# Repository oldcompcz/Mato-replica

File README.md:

# Mato-replica
Mato computer replica

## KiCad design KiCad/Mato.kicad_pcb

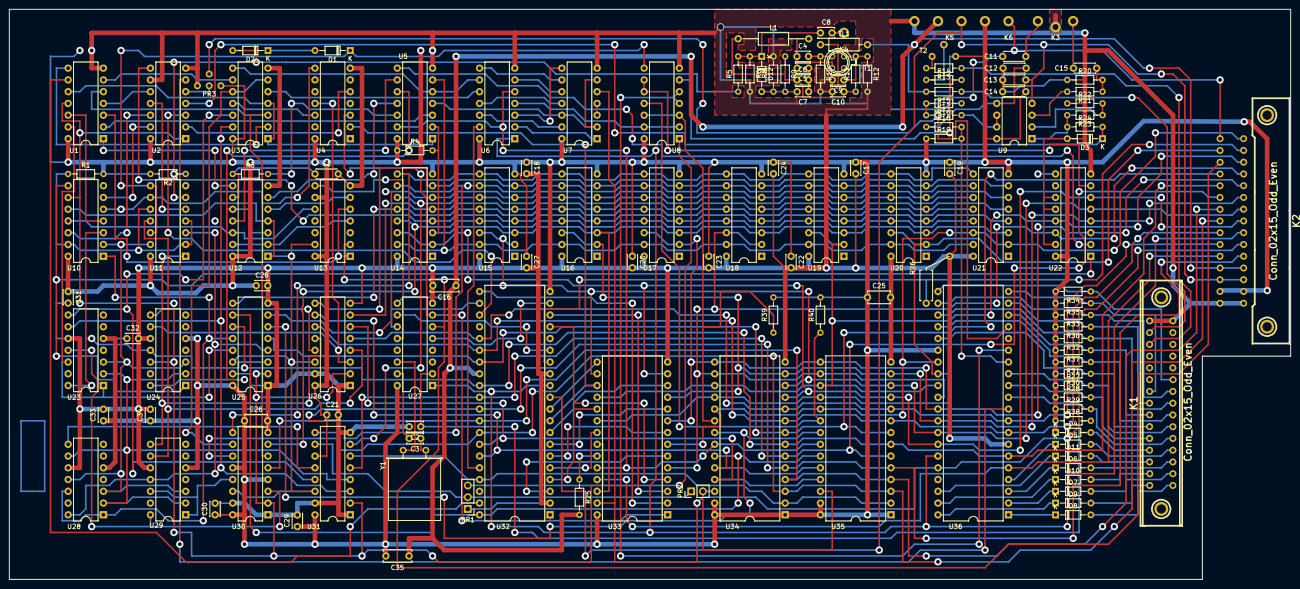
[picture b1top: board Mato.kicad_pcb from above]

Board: 4 copper layers, 276.9 x 123.2 mm, 136 parts (0 on the bottom side), 184 nets.

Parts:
C1: 220p; C_Disc_D4.3mm_W1.9mm_P5.00mm
C2: 1M; C_Disc_D3.4mm_W2.1mm_P2.50mm
C3: 8p2; C_Disc_D3.4mm_W2.1mm_P2.50mm
C4: 6p8; C_Disc_D3.0mm_W2.0mm_P2.50mm
C5: 18p; C_Disc_D3.0mm_W2.0mm_P2.50mm
C6: 10p; C_Disc_D3.0mm_W2.0mm_P2.50mm
C7: 2p2; C_Disc_D3.0mm_W2.0mm_P2.50mm
C8: 22p; C_Disc_D3.4mm_W2.1mm_P2.50mm
C9: 100p; C_Disc_D3.0mm_W2.0mm_P2.50mm
C10: 3n3; C_Disc_D3.0mm_W2.0mm_P2.50mm
C11: M1; C_Disc_D4.3mm_W1.9mm_P5.00mm
C12, C13, C14: 100n; C_Disc_D4.3mm_W1.9mm_P5.00mm
C15: 1M; C_Disc_D4.3mm_W1.9mm_P5.00mm
C16, C35: 68n; C_Disc_D6.0mm_W2.5mm_P5.00mm
C17, C18, C19, C20, C21, C22, C23, C24, C27, C28, C34: 68n; C_Disc_D3.0mm_W2.0mm_P2.50mm
C25, C26: 68n; C_Disc_D4.7mm_W2.5mm_P5.00mm
C29, C30, C31, C32, C33: CP; C_Disc_D3.0mm_W2.0mm_P2.50mm
D1, D2, D6, D7, D8, D9, D10, D11: D; D_DO-34_SOD68_P7.62mm_Horizontal
D3, D4: KA261; D_DO-34_SOD68_P7.62mm_Horizontal
D5: 7 x KA 261; D_DO-34_SOD68_P7.62mm_Horizontal
D12: KA206; D_DO-34_SOD68_P7.62mm_Horizontal
K1: Conn_02x15_Odd_Even; TX5133012-mato
K2: Conn_02x15_Odd_Even; TX5133011-mato
K3: K3; mato-K3
K4: Conn_01x02_Female; mato-K6
K5: Power; mato-power
K6: K6; mato-K6
L1: L; R_Axial_DIN0207_L6.3mm_D2.5mm_P15.24mm_Horizontal
PR1: mato-pr1; PinHeader_1x03_P2.54mm_Vertical
PR2: Jumper_NO_Small; PinHeader_1x02_P2.54mm_Vertical
PR3: 4-point-link; mato-pr3
R1: 2K7; R_Axial_DIN0204_L3.6mm_D1.6mm_P7.62mm_Horizontal
R2: 470R; R_Axial_DIN0204_L3.6mm_D1.6mm_P7.62mm_Horizontal
R3: 100R; R_Axial_DIN0204_L3.6mm_D1.6mm_P7.62mm_Horizontal
R4: 270R; R_Axial_DIN0204_L3.6mm_D1.6mm_P7.62mm_Horizontal
R5: 1K2; R_Axial_DIN0204_L3.6mm_D1.6mm_P7.62mm_Horizontal
R6, R10, R14, R16, R18, R19, R22, R25, R39, R40: 1K; R_Axial_DIN0204_L3.6mm_D1.6mm_P7.62mm_Horizontal
R8: 6K8; R_Axial_DIN0204_L3.6mm_D1.6mm_P7.62mm_Horizontal
R9, R27, R28, R29, R30, R31, R32, R33, R34, R35, R36, R37: 18K; R_Axial_DIN0204_L3.6mm_D1.6mm_P7.62mm_Horizontal
R11: 8K2; R_Axial_DIN0204_L3.6mm_D1.6mm_P7.62mm_Horizontal
R12: 2K2; R_Axial_DIN0204_L3.6mm_D1.6mm_P7.62mm_Horizontal
R13: 56R; R_Axial_DIN0204_L3.6mm_D1.6mm_P7.62mm_Horizontal
R15: 180R; R_Axial_DIN0204_L3.6mm_D1.6mm_P7.62mm_Horizontal
R17, R20: 10K; R_Axial_DIN0204_L3.6mm_D1.6mm_P7.62mm_Horizontal
R21: 4K7; R_Axial_DIN0204_L3.6mm_D1.6mm_P7.62mm_Horizontal
R23: 82K; R_Axial_DIN0204_L3.6mm_D1.6mm_P7.62mm_Horizontal
R24: 130; R_Axial_DIN0204_L3.6mm_D1.6mm_P7.62mm_Horizontal
R26: 270R; R_Axial_Bend
R38: M22; R_Axial_DIN0204_L3.6mm_D1.6mm_P7.62mm_Horizontal
T1: KF 524; KF524
T2: KC 307; mato-kc307
TL1: L; R_Axial_DIN0207_L6.3mm_D2.5mm_P10.16mm_Horizontal
U1, U6: 7404; DIP-14_W7.62mm
U2: 7486; DIP-14_W7.62mm
U3, U7, U12: 7400; DIP-14_W7.62mm
U4: 7474; DIP-14_W7.62mm
U5, U10: 7410; DIP-14_W7.62mm
U8: 7403; DIP-14_W7.62mm
U9: LM1458; DIP-8_W7.62mm
U11: 7405; DIP-14_W7.62mm
U13: 74164; DIP-14_W7.62mm
U14, U15, U16, U17, U18, U19, U20, U21: 4164; DIP-16_W7.62mm
U22: 74165; DIP-16_W7.62mm
U23, U24, U28, U29: 7493; DIP-14_W7.62mm
U25, U26, U30, U31: 74153; DIP-16_W7.62mm
U27: 8224; DIP-16_W7.62mm
U32: 8080A; DIP-40_W15.24mm
U33: 8228; DIP-28_W15.24mm
U34, U35: 27C64/128; DIP-28_W15.24mm
U36: 8255; DIP-40_W15.24mm
Y1: Crystal; Crystal_HC18-U_Horizontal

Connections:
+5V: C14.2, C17.1, C18.1, C19.1, C20.1, C21.1, C22.1, C23.1, C24.1, C25.1, C26.1, C27.1, C28.1, C29.1, C30.1, C31.1, C32.1, C33.1, C34.1, C35.2, D4.1, K2.27, K2.28, K5.4, PR3.6, R1.2, R2.2, R4.1, R15.2, R19.1, R27.1, R28.1, R29.1, R30.2, R31.2, R32.2, R33.2, R34.2, R35.2, R36.2, R37.2, R38.1, R39.2, R40.2, T2.3, TL1.2, U1.14, U2.14, U3.14, U4.14, U5.14, U6.14, U7.14, U8.14, U9.8, U10.14, U11.14, U12.14, U13.9, U13.14, U14.8, U15.8, U16.8, U17.8, U18.8, U19.8, U20.8, U21.8, U22.16, U23.5, U24.5, U25.16, U26.16, U27.16, U28.5, U29.5, U30.4, U30.12, U30.16, U31.16, U32.20, U33.28, U34.1, U34.27, U34.28, U35.1, U35.27, U35.28, U36.26
+12V: C16.1, C35.1, K2.23, K2.24, K5.2, R25.2, U27.9, U32.28
-5V: C13.2, K2.25, K2.26, K5.3, U9.4, U32.11
/PIO/CONT: K1.21, R29.2, U36.11
/PIO/LED1: K1.4, R15.1
/PIO/REPRO: K1.6, R13.1
/PIO/SHIFT: K1.22, R28.2, U36.12
/PIO/STOP: K1.19, R27.2, U36.13
/RAM/addr0: U14.5, U15.5, U16.5, U17.5, U18.5, U19.5, U20.5, U21.5, U26.7
/RAM/addr1: U14.7, U15.7, U16.7, U17.7, U18.7, U19.7, U20.7, U21.7, U26.9
/RAM/addr2: U14.6, U15.6, U16.6, U17.6, U18.6, U19.6, U20.6, U21.6, U25.7
/RAM/addr3: U14.12, U15.12, U16.12, U17.12, U18.12, U19.12, U20.12, U21.12, U25.9
/RAM/addr4: U14.11, U15.11, U16.11, U17.11, U18.11, U19.11, U20.11, U21.11, U31.7
/RAM/addr5: U14.10, U15.10, U16.10, U17.10, U18.10, U19.10, U20.10, U21.10, U31.9
/RAM/addr6: U14.13, U15.13, U16.13, U17.13, U18.13, U19.13, U20.13, U21.13, U30.7
/RAM/addr7: U14.9, U15.9, U16.9, U17.9, U18.9, U19.9, U20.9, U21.9, U30.9
/READY: U2.3, U32.23
/STSTB: U4.3, U27.7, U33.1
/SYNC: U27.5, U32.19
/modulator/TV-VIDEO: C8.2, K4.1
A0: K2.20, U26.5, U32.25, U34.10, U35.10, U36.9
A1: K2.18, U26.11, U32.26, U34.9, U35.9, U36.8
A2: K2.8, U25.5, U32.27, U34.8, U35.8
A3: K2.10, U25.11, U32.29, U34.7, U35.7, U36.6
A4: K2.12, U31.5, U32.30, U34.6, U35.6
A5: K2.21, U31.11, U32.31, U34.5, U35.5
A6: K2.14, U30.5, U32.32, U34.4, U35.4
A7: K2.16, U30.11, U32.33, U34.3, U35.3
A8: U26.6, U32.34, U34.25, U35.25
A9: U26.10, U32.35, U34.24, U35.24
A10: U25.6, U32.1, U34.21, U35.21
A11: U25.10, U32.40, U34.23, U35.23
A12: U31.6, U32.37, U34.2, U35.2
A13: PR1.2, PR2.1, U31.10, U32.38
A14: U1.9, U32.39
A14*: U1.5, U3.3, U30.6
A15: U6.13, U32.36
A15*: U3.6, U3.10, U30.10
CAS: U5.10, U12.3, U12.10, U24.14
COMPOSITE: D2.2, R2.1, R5.1, U11.6
CSROM0: R40.1, U8.11, U35.20
CSROM1: R39.1, U8.3, U8.12, U34.20
D0: K2.15, U14.2, U14.14, U22.6, U33.13, U34.11, U35.11, U36.34
D1: K2.13, U15.2, U15.14, U22.5, U33.16, U34.12, U35.12, U36.33
D2: K2.11, U16.2, U16.14, U22.4, U33.11, U34.13, U35.13, U36.32
D3: K2.9, U17.2, U17.14, U22.3, U33.9, U34.15, U35.15, U36.31
D4: K2.7, U18.2, U18.14, U22.14, U33.5, U34.16, U35.16, U36.30
D5: K2.5, U19.2, U19.14, U22.13, U33.18, U34.17, U35.17, U36.29
D6: K2.4, U20.2, U20.14, U33.20, U34.18, U35.18, U36.28
D7: K2.1, U21.2, U21.14, U33.7, U34.19, U35.19, U36.27
GND: C1.2, C2.2, C9.2, C10.2, C12.2, C13.1, C14.1, C16.2, C17.2, C18.2, C19.2, C20.2, C21.2, C22.2, C23.2, C24.2, C25.2, C26.2, C27.2, C28.2, C29.2, C30.2, C31.2, C32.2, C33.2, C34.2, D3.2, K1.1, K1.2, K2.29, K2.30, K3.3, K5.1, PR1.1, PR3.4, R6.2, R8.2, R10.2, R12.2, R16.1, R20.1, R22.1, R26.2, U1.7, U2.7, U2.9, U3.7, U4.7, U5.7, U6.7, U7.7, U8.7, U10.7, U11.7, U12.7, U13.7, U14.16, U15.16, U16.16, U17.16, U18.16, U19.16, U20.16, U21.16, U22.8, U22.11, U22.12, U22.15, U23.10, U24.10, U25.1, U25.8, U25.15, U26.1, U26.8, U26.15, U27.8, U28.10, U29.10, U30.1, U30.8, U30.15, U31.1, U31.8, U31.15, U32.2, U32.13, U33.14, U34.14, U35.14, U36.7
INT: K2.3, R26.1, U32.14
unnamed: C1.1, R3.1, U12.9
unnamed: C3.1, Y1.2
unnamed: C3.2, U27.15
unnamed: C4.1, C5.2, L1.2, T1.3
unnamed: C4.2, R10.1, T1.1
unnamed: C5.1, C6.2, C7.1
unnamed: C7.2, D12.2, R8.1, R9.2
unnamed: C8.1, D12.1, R5.2, R6.1
unnamed: C9.1, R11.2, R12.1, T1.2
unnamed: C6.1, C10.1, L1.1, R9.1, R11.1, TL1.1
unnamed: C11.1, R16.2, R17.1
unnamed: C11.2, K3.1
unnamed: C12.1, R18.1, U9.5
unnamed: C15.1, R20.2, R21.1
unnamed: C15.2, K3.2
unnamed: D1.1, U8.8, U11.8, U11.12
unnamed: D1.2, D2.1
unnamed: D3.1, R24.2, U2.4
unnamed: D5.1, U36.4
unnamed: D5.2, K1.23
unnamed: D6.1, U36.3
unnamed: D6.2, K1.25
unnamed: D7.1, U36.2
unnamed: D7.2, K1.27
unnamed: D8.1, U36.1
unnamed: D8.2, K1.29
unnamed: D9.1, U36.40
unnamed: D9.2, K1.30
unnamed: D10.1, U36.39
unnamed: D10.2, K1.28
unnamed: D11.1, U36.38
unnamed: D11.2, K1.26
unnamed: K1.11, R34.1, U36.21
unnamed: K1.13, R33.1, U36.22
unnamed: K1.14, R35.1, U36.20
unnamed: K1.15, R32.1, U36.23
unnamed: K1.16, R36.1, U36.19
unnamed: K1.17, R31.1, U36.24
unnamed: K1.18, R37.1, U36.18
unnamed: K1.20, R30.1, U36.25
unnamed: K2.2, K6.1
unnamed: PR1.3, U8.1
unnamed: PR2.2, U34.26, U35.26
unnamed: PR3.5, U2.5
unnamed: PR3.7, U36.17
unnamed: R1.1, U10.13, U11.2, U11.4, U11.10
unnamed: R3.2, U5.12
unnamed: R13.2, T2.1
unnamed: R14.1, T2.2
unnamed: R14.2, U8.6
unnamed: R17.2, U9.6, U9.7
unnamed: R18.2, R19.2, U36.14
unnamed: R21.2, U9.3
unnamed: R22.2, R23.1, U9.2
unnamed: R23.2, R24.1, U9.1
unnamed: R25.1, U33.23
unnamed: U1.1, U12.8
unnamed: U1.2, U5.3
unnamed: U1.3, U13.5
unnamed: U1.4, U2.10
unnamed: U1.6, U3.9
unnamed: U1.8, U3.2
unnamed: U1.10, U3.1, U3.4, U5.1
unnamed: U1.12, U10.4
unnamed: U2.2, U4.5
unnamed: U2.6, U36.10
unnamed: U3.5, U6.10
unnamed: U3.8, U5.5, U6.9
unnamed: U3.11, U4.12
unnamed: U5.4, U7.2, U7.6, U7.12
unnamed: U6.2, U7.1
unnamed: U6.3, U7.8
unnamed: U6.4, U8.2, U8.13
unnamed: U6.6, U7.10
unnamed: U6.8, U7.9
unnamed: U6.11, U7.11
unnamed: U6.12, U7.13
unnamed: U7.3, U7.4
unnamed: U10.2, U11.13, U23.3, U24.3, U28.3, U28.11, U29.3
unnamed: U4.8, U10.5, U11.9
unnamed: U2.13, U10.6
unnamed: U10.11, U12.12, U13.10
unnamed: U2.12, U10.12
unnamed: U2.11, U11.5
unnamed: U12.5, U13.6
unnamed: U5.11, U12.6
unnamed: U5.9, U12.11
unnamed: U12.2, U12.13, U13.4
unnamed: U8.9, U8.10, U22.7
unnamed: U27.10, U32.15
unnamed: U27.11, U32.22
unnamed: U27.14, Y1.1
unnamed: U32.3, U33.6
unnamed: U32.4, U33.19
unnamed: U32.5, U33.21
unnamed: U32.6, U33.8
unnamed: U32.7, U33.10
unnamed: U32.8, U33.12
unnamed: U32.10, U33.15
unnamed: U32.17, U33.4
unnamed: U32.18, U33.3
unnamed: U32.21, U33.2
unnamed: U8.4, U8.5, U36.15
OSC: U13.8, U27.12
PH2(TTL): K2.6, U13.1, U13.2, U27.6
R0: U4.11, U24.9, U26.3
R1: U24.8, U26.13
R2: U10.3, U23.14, U24.11, U25.3
R3: U1.13, U23.1, U23.12, U25.13
R4: U3.13, U23.9, U31.3
R5: U3.12, U23.8, U31.13
R6: U23.11, U29.14, U30.3
R7: U29.1, U29.12, U30.13
R8: U11.11, U26.4, U29.9
R9: U11.1, U26.12, U29.8
R10: U11.3, U25.4, U28.14, U29.11
R11: U10.1, U25.12, U28.1, U28.12
R12: U23.2, U24.2, U28.2, U28.9, U29.2, U31.4
R13: U28.8, U31.12
RESET: K2.17, U6.1, U27.1, U32.12, U36.35
RESMAN: C2.1, D4.2, K1.24, R38.2, U27.2
VIDEO: U1.11, U2.1, U10.9, U24.12, U25.2, U26.2, U30.2, U31.2, U33.22
VIDEOCL: U5.8, U22.2
privD1: U4.2, U32.9, U33.17
¬AMUX: U10.10, U12.1, U12.4, U13.13, U25.14, U26.14, U30.14, U31.14
¬CAS: U5.6, U14.15, U15.15, U16.15, U17.15, U18.15, U19.15, U20.15, U21.15
¬IORD: K2.22, U33.25, U36.5
¬IOWR: K2.19, U7.5, U33.27, U36.36
¬MRD: U5.13, U6.5, U33.24, U34.22, U35.22
¬MWR: R4.2, U5.2, U14.3, U15.3, U16.3, U17.3, U18.3, U19.3, U20.3, U21.3, U33.26
¬RAS: U2.8, U14.4, U15.4, U16.4, U17.4, U18.4, U19.4, U20.4, U21.4
¬STB: U10.8, U22.1, U24.1

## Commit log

2021-08-25 fixes
2023-02-25 add Keyboard
